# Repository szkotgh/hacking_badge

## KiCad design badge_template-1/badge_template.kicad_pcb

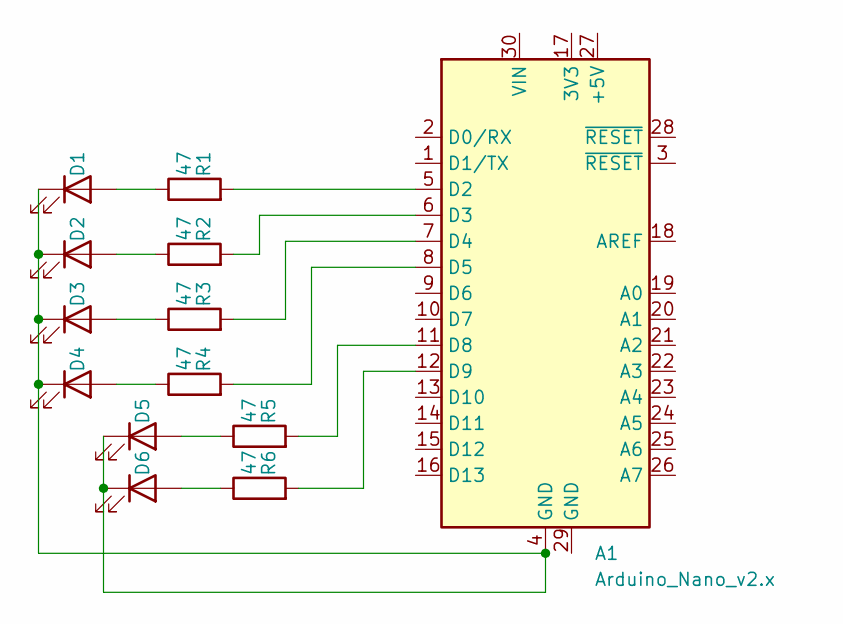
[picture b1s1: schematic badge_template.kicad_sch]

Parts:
A1: Arduino_Nano_v2.x; Arduino_Nano
D1, D2, D3, D4, D5, D6: LED; LED_0603_1608Metric
R1, R2, R3, R4, R5, R6: 47; LED_0201_0603Metric

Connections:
unnamed: A1.5 (D2), R1.2
unnamed: A1.6 (D3), R2.2
unnamed: A1.7 (D4), R3.2
unnamed: A1.8 (D5), R4.2
unnamed: A1.11 (D8), R5.2
unnamed: A1.12 (D9), R6.2
unnamed: D1.2 (A), R1.1
unnamed: A1.4 (GND), D1.1 (K), D2.1 (K), D3.1 (K), D4.1 (K), D5.1 (K), D6.1 (K)
unnamed: D2.2 (A), R2.1
unnamed: D3.2 (A), R3.1
unnamed: D4.2 (A), R4.1
unnamed: D5.2 (A), R5.1
unnamed: D6.2 (A), R6.1

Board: 2 copper layers, 13 parts (4 on the bottom side), 13 nets, no tracks yet.

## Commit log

2024-12-06 update: pcb update
2025-05-09 update: update
